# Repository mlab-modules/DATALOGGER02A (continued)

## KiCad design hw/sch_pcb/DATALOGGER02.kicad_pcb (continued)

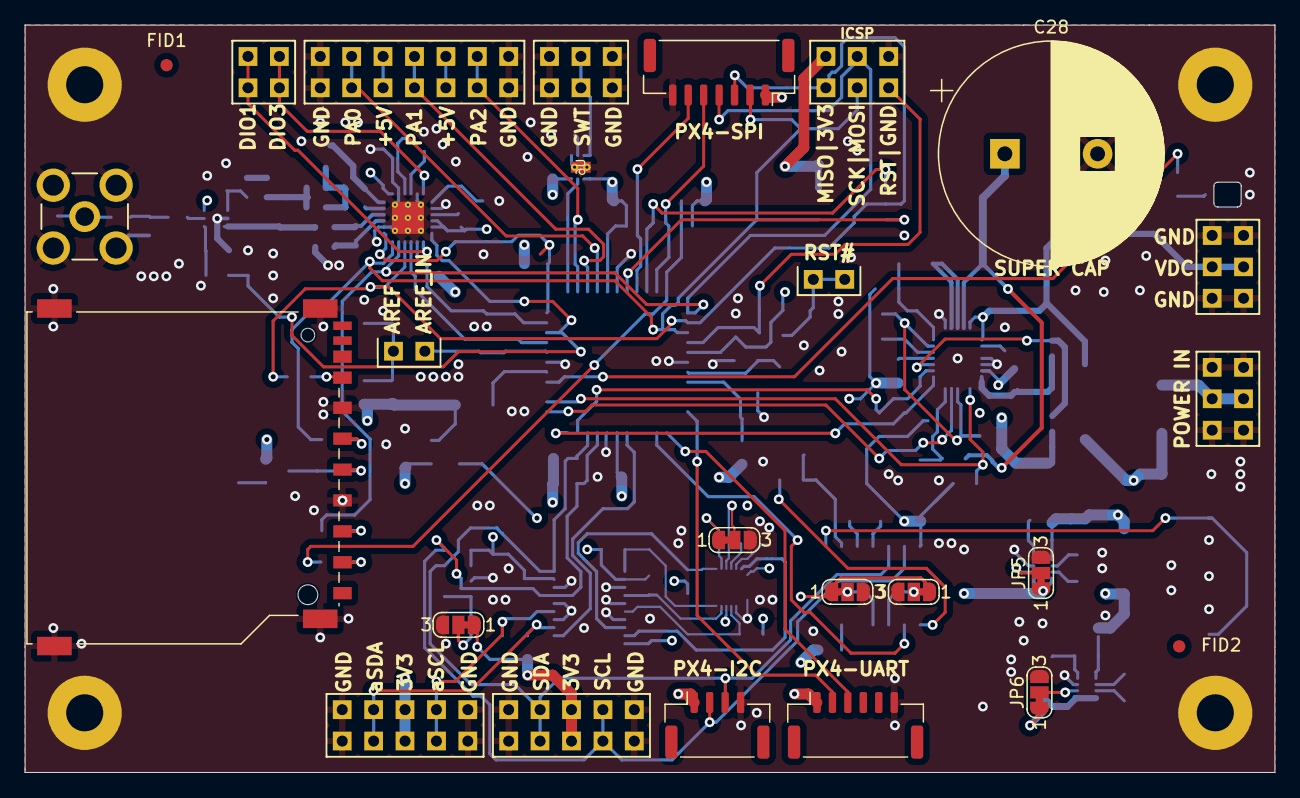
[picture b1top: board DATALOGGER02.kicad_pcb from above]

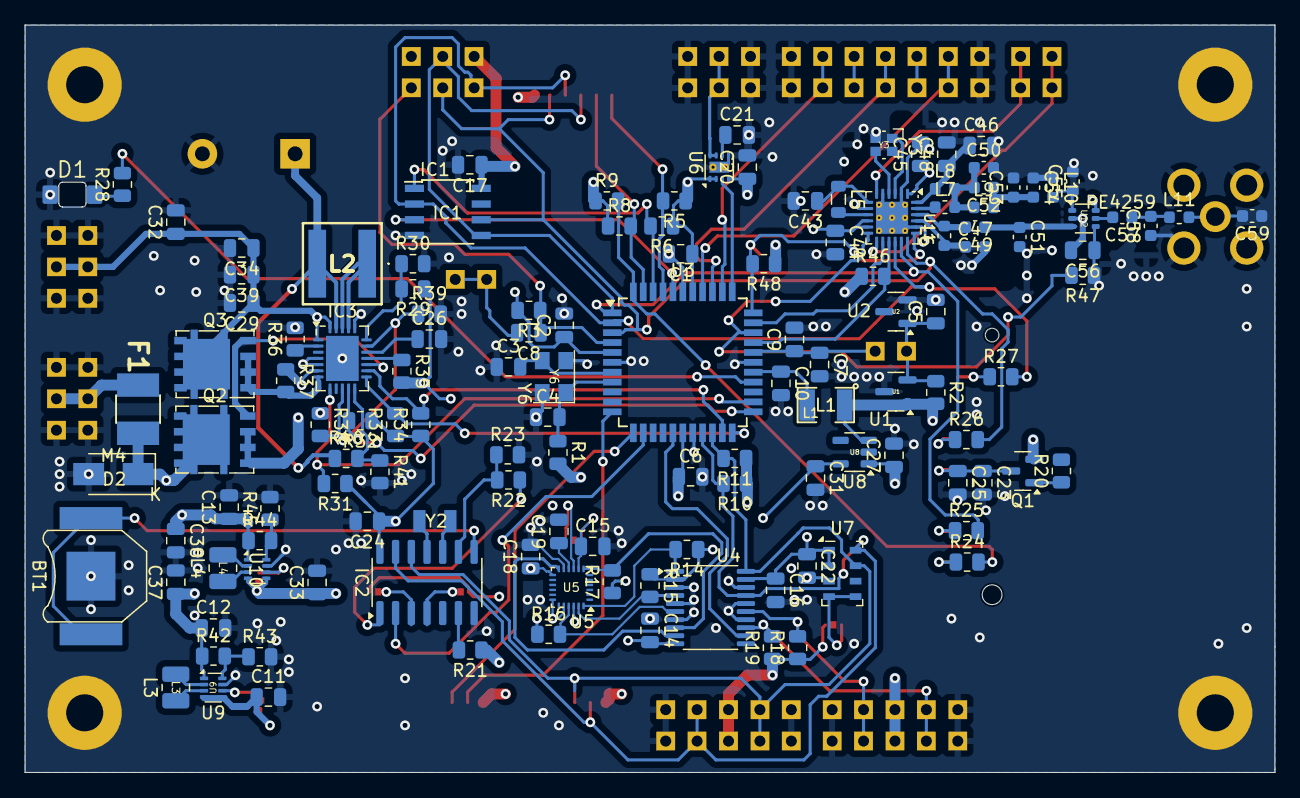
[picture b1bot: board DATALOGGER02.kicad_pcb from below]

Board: 4 copper layers, 101.1 x 60.5 mm, 160 parts (132 on the bottom side), 105 nets.

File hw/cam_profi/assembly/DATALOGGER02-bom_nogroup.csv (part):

Component,Description,Part,References,Value,Footprint,Quantity Per PCB,Datasheet,ust_id,mfpn,height,mouser part number,mouser price/stock,manufacturer_name,manufacturer_part_number
1,,Battery_Cell-device,BT1,Battery_Cell-device 3V,BatteryHolder_Keystone_2998_1x6.8mm,1,,5c70984412875079b91f87ec,,,,,,
2,,C-Device-ISM02A-rescue,C47,1p8,SMD-0805,1,,5dad52a4128750448eca18e8,"C0G 0,1pF 50V",,,,,
3,,C-Device-ISM02A-rescue,C55,2p2,SMD-0805,1,,5c70984812875079b91f8bdd,"C0G 0,1pF 50V",,,,,
4,,C-Device-ISM02A-rescue,C49,2p4,SMD-0805,1,,5dad53d8128750448eca1906,"C0G 0,1pF 50V",,,,,
5,,C-Device-ISM02A-rescue,C52C58C59,3p3,SMD-0805,3,,5cd09016128750448e45434f,"C0G 0,1pF 50V",,,,,
6,,C-Device-ISM02A-rescue,C53,5p6,SMD-0805,1,,5dad5450128750448eca1919,"C0G 0,25pF 50V",,,,,
7,,C-device,C3C4,15pF,SMD-0805,2,,5c70984712875079b91f8b32,,,,,,
8,,C-Device-ISM02A-rescue,C54C57,39pF,SMD-0805,2,,5dad549f128750448eca1926,C0G 5% 50V,,,,,
9,,C-Device-ISM02A-rescue,C48,47pF,SMD-0805,1,,5dad5314128750448eca18f7,C0G 5% 50V,,,,,
10,,C-device,C21,1nF,SMD-0805,1,,5c70984712875079b91f8b45,,,,,,
11,Unpolarized capacitor,C,C26C56,1nF,SMD-0805,2,~,5c70984812875079b91f8bec,,,,,,
12,,C-Device-ISM02A-rescue,C46,47nF,SMD-0805,1,,5dad51cf128750448eca18d8,X7R 1% 16V,,,,,
13,,C-device,C1C2C5C6C9C10C17C25C32C37C38,100nF,SMD-0805,11,,5c70984712875079b91f8b4c,,,,,,
14,Unpolarized capacitor,C,C14C15C16C18C19C22C24,100nF,SMD-0805,7,~,5c70984712875079b91f8b4c,,,,,,
15,,C-Device-ISM02A-rescue,C45,100nF,SMD-0805,1,,5c70984812875079b91f8bf2,,,,,,
16,,C-Device-ISM02A-rescue,C43,470nF,SMD-0805,1,,5dad50c1128750448eca18c6,X5R 10% 10V,,,,,
17,,C-device,C20,1uF,SMD-0805,1,,5c70984712875079b91f8b50,,,,,,
18,Unpolarized capacitor,C,C27C31,1uF,SMD-0805,2,~,5c70984712875079b91f8b50,,,,,,
19,,C-Device-ISM02A-rescue,C44,1uF,SMD-0805,1,,5c70984812875079b91f8bc2,,,,,,
20,,C-device,C8,4u7,SMD-0805,1,,5c70984712875079b91f8b52,,,,,,
21,,C-device,C7C23,10uF,SMD-0805,2,,5c70984812875079b91f8bbd,,,,,,
22,,CP2,C39C40,22uF,TantalC_SizeB_Reflow,2,,,,,,,,
23,,CP2,C33C34,47uF,TantalC_SizeB_Reflow,2,,,,,,,,
24,,CP-device,C29,100uF,TantalC_SizeC_Reflow,1,,5c70984412875079b91f8867,,,,,,
25,,C-Device-ISM02A-rescue,C41C42C50C51,-,SMD-0805,4,,,,,,,,
26,Unpolarized capacitor,C,C28,50F,C_Radial_D16_L25_P7.5,1,~,,,,,,,
27,,EMI_Filter_C-device,C30C35C36,EMI_Filter_C,FIR_0805,3,http://www.murata.com/~/media/webrenewal/support/library/cat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,,,,,,,
28,,LED-device,D1,HLMP-K150+FIX-LED-313,LED_1206_mill,1,,5c70984712875079b91f8b67,,,,,,
29,,D-device,D2,M4,Diode-SMA_Standard,1,,5c70984512875079b91f88ac,,,,,,
30,,Polyfuse-device,F1,1.2A,1812,1,,5c70984512875079b91f88d2,,,,,,
31,F-RAM Excelon LP 40 MHz 8-EIAJ,CY15B108QN-40SXI,IC1,CY15B108QN-40SXI,SOIC-8_3.9x4.9mm_Pitch1.27mm,1,https://www.mouser.in/datasheet/2/196/CYPR_S_A0011123055_1-3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,,,2.03,727-CY15B108QN-40SXI,https://www.mouser.co.uk/ProductDetail/Infineon-Cypress/CY15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,Infineon / Cypress,CY15B108QN-40SXI
32,-40C to +85C Integrated Processor Companion with Memory 14-pin SOIC Package,FM3164-S,IC2,FM3164-G,SOIC-14,1,https://4donline.ihs.com/images/VipMasterIC/IC/RAMT/RAMTS003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,,,1.75,,,RAMTRON,FM3164-S
33,Power Management Specialized - PMIC 2.5A Supercapacitor Backup Power Manager,LTC4041EUFD#PBF,IC3,LTC4041EUFD#PBF,QFN-24-1EP_4x5mm_P0.5mm_EP2.65x3.65mm,1,https://www.analog.com/media/en/technical-documentation/data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,,,0.8,584-4041EUFDPB,https://www.mouser.co.uk/ProductDetail/Analog-Devices/LTC404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,Analog Devices,LTC4041EUFD#PBF
34,"Generic connector, single row, 01x03, script generated (kicad-library-utils/schlib/autogen/connector/)",Conn_01x03_Male,J19J20,Conn_01x03_Male,Straight_1x03,2,~,,,,,,,
35,"Generic connector, single row, 01x04, script generated (kicad-library-utils/schlib/autogen/connector/)",Conn_01x04_Female,J9,Conn_01x04_Female,JST_GH_SM04B-GHS-TB_1x04-1MP_P1.25mm_Horizontal,1,~,,,,,,,
36,"Generic connector, single row, 01x06, script generated (kicad-library-utils/schlib/autogen/connector/)",Conn_01x06_Female,J7,Conn_01x06_Female,JST_GH_SM06B-GHS-TB_1x06-1MP_P1.25mm_Horizontal,1,~,,,,,,,
37,"Generic connector, single row, 01x07, script generated (kicad-library-utils/schlib/autogen/connector/)",Conn_01x07_Female,J8,Conn_01x07_Female,JST_GH_SM07B-GHS-TB_1x07-1MP_P1.25mm_Horizontal,1,~,,,,,,,
38,,HEADER_2x01-MLAB_HEADER,J2,HEADER_2x01,Straight_2x01,1,,,,,,,,
39,,HEADER_2x01_PARALLEL-MLAB_HEADER,J1,HEADER_2x01_PARALLEL,Straight_2x01,1,,,,,,,,
40,"2x02 2.54 mm pitch header, 2 pins next to each other are connected",HEADER_2x02_PARALLEL,J13,HEADER_2x02_PARALLEL,Straight_2x02,1,,,,,,,,
41,,HEADER_2x03-MLAB_HEADER,J3,HEADER_2x03,Straight_2x03,1,,,,,,,,
42,"2x03 2.54 mm pitch header, 2 pins next to each other are connected",HEADER_2x03_PARALLEL,J5J24,HEADER_2x03_PARALLEL,Straight_2x03,2,,,,,,,,
43,,HEADER_2x03_PARALLEL-MLAB_HEADER,J4,HEADER_2x03_PARALLEL,Straight_2x03,1,,,,,,,,
44,"2x05 2.54 mm pitch header, 2 pins next to each other are connected",HEADER_2x05_PARALLEL,J10J12,HEADER_2x05_PARALLEL,Straight_2x05,2,,,,,,,,
45,"2x07 2.54 mm pitch header, 2 pins next to each other are connected",HEADER_2x07_PARALLEL,J11,HEADER_2x07_PARALLEL,Straight_2x07,1,,,,,,,,
46,,SD_Card-Connector,J6,MCC-SD (kouka z modulu),MCC-SD,1,http://portal.fciconnect.com/Comergent//fci/drawing/10067847.pdf,,,,,,,
47,,SMA-MLAB_CONNECTORS,J23,MCX,MCX,1,,,,,,,,
48,,L-Device-ISM02A-rescue,L7,0R,L_0402_1005Metric,1,,5c70984512875079b91f8949,,,,,,
49,,L-Device-ISM02A-rescue,L9,2n5,L_0402_1005Metric,1,,5dad56ff128750448eca1975,LQW15AN2N5C00D,,,,,
50,,L-Device-ISM02A-rescue,L10,4n7,L_0402_1005Metric,1,,5dad574f128750448eca1986,LQW15AN4N7C00D,,,,,
51,,L-Device-ISM02A-rescue,L11,9n1,L_0402_1005Metric,1,,5dad5789128750448eca1995,LQW15AN9N1H00D,,,,,
52,,L-Device-ISM02A-rescue,L6,15nH,L_0402_1005Metric,1,,5dad566c128750448eca1959,LQW15AN15NH00D,,,,,
53,,L-Device-ISM02A-rescue,L8,47nH,L_0402_1005Metric,1,,5dad56ba128750448eca1968,LQW15AN47NJ00D,,,,,
54,,L_Small-Device-ISM02A-rescue,L5,15uH,L_0402_1005Metric,1,,5dad55e8128750448eca1941,MLZ2012M150W 0805,,,,,
55,,L-device,L1,10uH - LQH32CN100K23L,SMD-1210,1,,5c70984412875079b91f87ff,,,,,,
56,Inductor,L,L3L4,1uH - DFE252012P-1R0M=P2,L_1008_2520Metric,2,~,,,,,,,
57,Inductor,L,L2,XAL-6030-182 1.8 uH,XAL6030181MEC,1,~,,,,,,,
58,"-4.3A Id, -12V Vds, 50mOhm Rds, P-Channel HEXFET Power MOSFET, SOT-23",IRLML6401,Q1,DMP2045UQ-7,SOT-23,1,https://www.infineon.com/dgdl/irlml6401pbf.pdf?fileId=5546d4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,,,,,,,
59,"0.2A Id, 200V Vds, N-Channel MOSFET, 2.6V Logic Level, TO-92",2N7000,Q2Q3,SIR424DP,TO-92_Inline,2,https://www.vishay.com/docs/70226/70226.pdf,,,,,,,
60,Resistor,R,R37,25mR,SMD-0805,1,~,,,,,,,
61,,R-device,R24R25R26R27,100,SMD-0805,4,,5c70984512875079b91f8977,,,,,,
62,Resistor,R,R47,100R,SMD-0805,1,~,5c70984512875079b91f8956,,,,,,
63,Resistor,R,R20,470R,SMD-0805,1,~,,,,,,,
64,Resistor,R,R36,2k,SMD-0805,1,~,,,,,,,
65,,R-device,R28,2k2,SMD-0805,1,,5c70984612875079b91f8990,,,,,,
66,,R-device,R2,4k7,SMD-0805,1,,5c70984612875079b91f8995,,,,,,
67,Resistor,R,R5R6R8R9R10R11R14R15R16R17R18R19R21R48,10k,SMD-0805,14,~,5c70984612875079b91f899f,,,,,,
68,,R-device,R3,10k,SMD-0805,1,,5c70984612875079b91f899f,,,,,,
69,,R-Device-ISM02A-rescue,R46,10k,SMD-0805,1,,5c70984512875079b91f8962,,,,,,
70,Resistor,R,R23R30,56k,SMD-0805,2,~,,,,,,,
71,Resistor,R,R43R45,91k,SMD-0805,2,~,,,,,,,
72,Resistor,R,R32R33R34R39R41,100k,SMD-0805,5,~,,,,,,,
73,Resistor,R,R22R29,150k,SMD-0805,2,~,,,,,,,
74,Resistor,R,R40,220k,SMD-0805,1,~,,,,,,,
75,Resistor,R,R44,511k,SMD-0805,1,~,,,,,,,
76,Resistor,R,R42,806k,SMD-0805,1,~,,,,,,,
77,Resistor,R,R31,1M,SMD-0805,1,~,,,,,,,
78,,R-device,R1,-,SMD-0805,1,,,,,,,,
79,Resistor,R,R38,523k (E96),SMD-0805,1,~,,,,,,,
80,Resistor,R,R35,6.2k 1/8W,SMD-0805,1,~,,,,,,,
81,,ATMEGA1284P-AU-atmel,U3,ATMEGA1284P-AU,TQFP-44_10x10mm_P0.8mm,1,http://www.atmel.com/Images/Atmel-8272-8-bit-AVR-microcontro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,5c70984412875079b91f888e,,,,,,
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
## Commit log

2023-01-04 datalogger02a
2023-01-04 Update actions products
2023-01-04 update assets submodule
2023-01-04 Remove production files for version 01A
2023-01-04 IMU schema
2023-01-09 update of schematics
2023-01-09 ltc4041 update
2023-01-09 Cleanup repository add gitignore.
2023-01-09 Project cleanup.
2023-01-10 remove zip backups.
2023-01-10 schematics update - LTC4041, TPS631000
2023-05-25 automated commit; add github actions
2023-05-25 Update metadata files
2023-05-28 Update workflow files
2023-07-05 automated commit; rename source files to new naming convence
2023-09-15 Cleanup of repository.
2023-09-15 Update metadata.yaml
    Set status to "in development"
2023-09-16 Update image to image_title
2023-09-17 Update metadata.yaml
    select title image.
2024-09-29 Removing Li-ion accumulator BMS Adding ISM02B LoRa telemetry block.
2025-01-03 schematics update
2025-01-20 progress?
2025-01-22 another updates
2025-01-22 silkmasks done
2025-01-22 checks 'passed'
2025-01-22 Remove lock files to allow opening of project.
2025-01-22 Add lock files to gitignore.
2025-01-22 Update components from libraries. Improve schematics. Resolve some ERC and DRC errors.
2025-01-23 Update footprints. Improve layout Fix some DRC errors. Set components values matching inventory.
2025-01-23 Fix component placement and layout of telemetry transceiver.
